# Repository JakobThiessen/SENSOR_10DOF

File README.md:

# SENSOR_10DOF

- ACC/Gyro	(BMI160/323)
- ACC/Mag	(LSM303AGR)
- T/P/RH	(BME280)

# Hardware

| Top side                |Bottom side               |
|-----------------------:|:-------------------------:|
|  |  |

| Values                 | Reference                 |
|-----------------------:|:-------------------------:|
|  |  |

# Software

**BMI160:**
```diff
+ 0x68 --> SDO to GND (default)
# 0x69 --> SDO to VDDIO
```

**BMI323:**
```diff
+ 0x68 --> SDO to GND (default)
# 0x69 --> SDO to VDDIO
```

**BME280:**
```diff
+ 0x76 --> SDO to GND (default)
# 0x77 --> SDO to VDDIO
```

**LSM303AGR:**
```diff
+ 0x3A --> ACC (default)
+ 0x3C --> MAG (default)
```

## Driver

### lsm303agr

Standard C platform-independent drivers for MEMS motion and environmental sensors
- https://www.st.com/en/embedded-software/c-driver-mems.html
- https://github.com/STMicroelectronics/x-cube-mems1

Arduino/Grove
- https://github.com/Seeed-Studio/Grove_6Axis_Accelerometer_And_Compass/blob/master/examples/CompensatedCompass.ino

embedded/lsm303agr

``` c
/* USER CODE BEGIN PV */
static struct lsm303agr_dev Sensor;

/* USER CODE BEGIN 0 */
int8_t i2c_1_read(uint8_t dev_addr, uint8_t reg_addr, uint8_t *data, uint16_t len)
{
	int8_t result;

	result = HAL_I2C_Master_Transmit(&hi2c1, (uint16_t) dev_addr, &reg_addr, 1, 10);
	result += HAL_I2C_Master_Receive(&hi2c1, (uint16_t) dev_addr, data, len, 10);
	return result;
}

int8_t i2c_1_write(uint8_t dev_addr, uint8_t reg_addr, uint8_t *data, uint16_t len)
{
	int8_t result;
	uint8_t buffer[128];

	buffer[0] = reg_addr;
	memcpy(&buffer[1], data, len);

	result = HAL_I2C_Master_Transmit(&hi2c1, (uint16_t) dev_addr, buffer, len + 1, 100);
	return result;
}

void main(void)
{
	/* Hardware init*/
	
	........
	/*  */
	Sensor.dev_addr_mag = LSM303AGR_MAG_I2C_ADDRESS;
	Sensor.dev_addr_acc = LSM303AGR_ACC_I2C_ADDRESS;
	Sensor.read = i2c_1_read;
	Sensor.write = i2c_1_write;

	struct lsm303agr_mag_data magData;
	struct lsm303agr_acc_data accData;

	int8_t res = lsm303agr_mag_init(LSM303AGR_CONTINUOUS, &Sensor);
	res = lsm303agr_acc_init(LSM303AGR_ACC_NORMAL_MODE, &Sensor);

	...

	while (1)
	{
		int8_t rslt = 0;

		rslt = lsm303agr_mag_read_data(&magData, &Sensor);
		
		uint8_t data_ready_status = 0;
		lsm303agr_acc_get_DataReadyStatus(&data_ready_status, &Sensor);
		
		if (data_ready_status != 0)
		{
			lsm303agr_acc_read_data(&accData, &Sensor);
			rslt += lsm303agr_temp_read_data(&temperature, &Sensor);
		}
	}
}

```

### BMI160/323:

- https://github.com/boschsensortec/BMI160_driver
- https://github.com/boschsensortec/BMI323-Sensor-API

## Calibration of Magnetometer with Acc-Sensor

Application note: AN3192 Using LSM303DLH for a tilt compensated electronic compass

Masterarbeit
- https://reposit.haw-hamburg.de/bitstream/20.500.12738/8460/1/Masterarbeit_Tobias_Michaelsen.pdf

Lib von ST
- https://github.com/STMicroelectronics/x-cube-mems1

Eine Sammlung von Links zu dem Thema
- https://github.com/Seeed-Studio/Grove_6Axis_Accelerometer_And_Compass/blob/master/examples/CompensatedCompass.ino

- https://www.nxp.com/docs/en/application-note/AN4248.pdf
- https://www.nxp.com/docs/en/application-note/AN4249.pdf
- https://www.st.com/resource/en/design_tip/dt0058-computing-tilt-measurement-and-tiltcompensated-ecompass-stmicroelectronics.pdf
- https://www.bosch-sensortec.com/media/boschsensortec/downloads/datasheets/bst-bmm150-ds001.pdf

## Kalmanfilter
- https://www.cbcity.de/das-kalman-filter-einfach-erklaert-teil-1
- https://www.cbcity.de/das-kalman-filter-einfach-erklaert-teil-2
- https://www.cbcity.de/4d-kalman-filter-in-c
  
- https://www.halvorsen.blog/documents/automation/kalman_filter/LabVIEW%20Kalman%20Filter%20Examples.pdf

## Rotationsmatrix
- https://www.cbcity.de/tutorial-rotationsmatrix-und-quaternion-einfach-erklaert-in-din70000-zyx-konvention

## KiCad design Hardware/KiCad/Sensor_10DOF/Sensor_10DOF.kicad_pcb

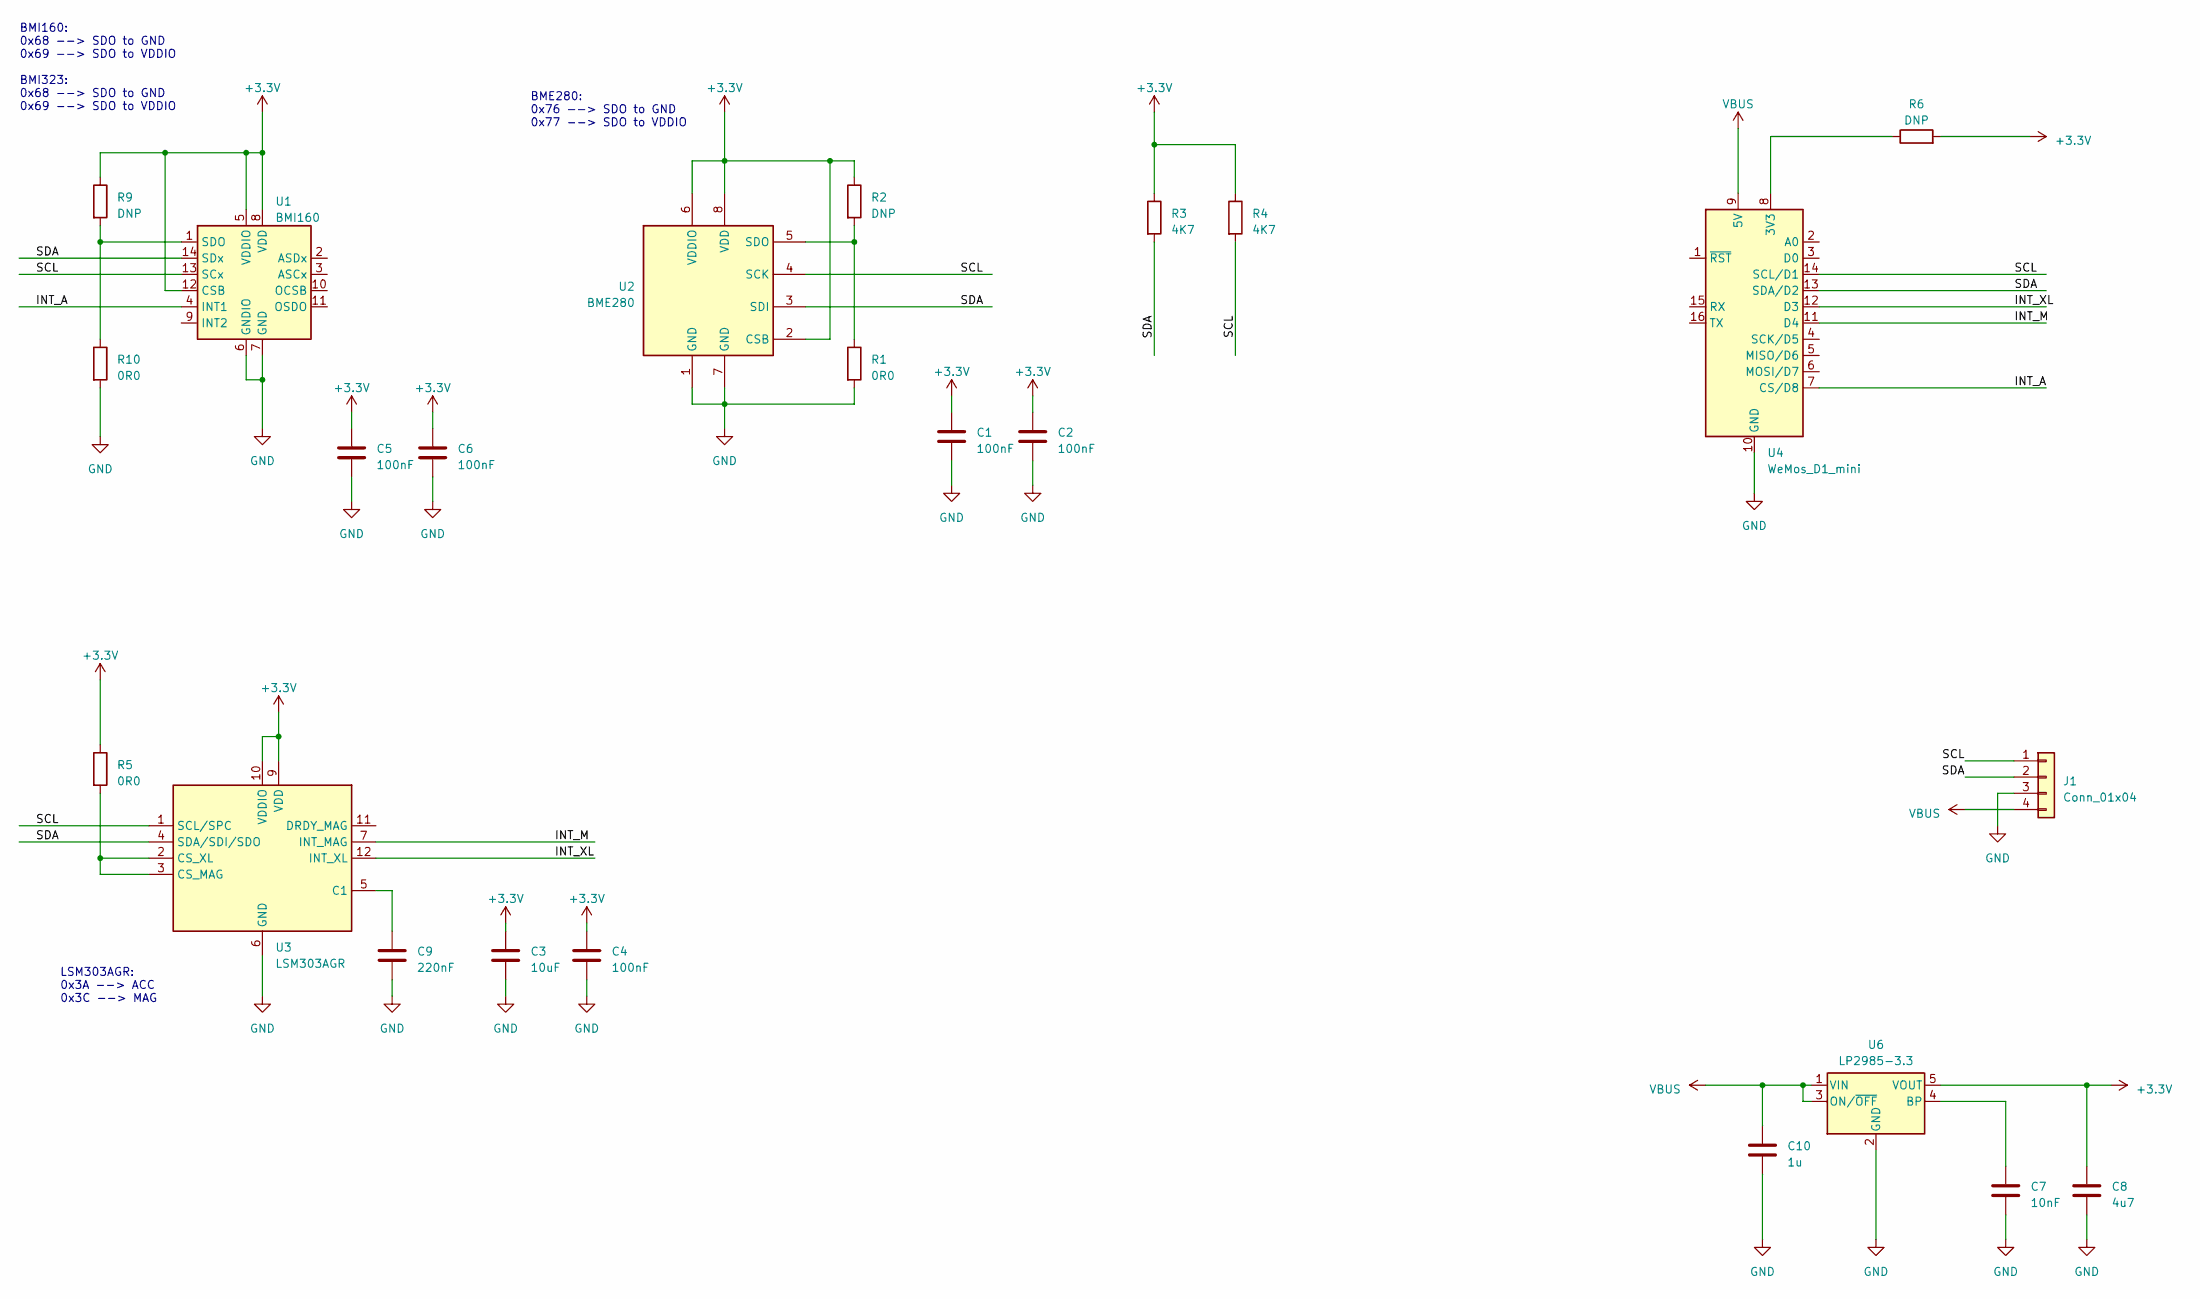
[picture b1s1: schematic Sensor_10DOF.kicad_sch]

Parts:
C1, C2, C4, C5, C6: 100nF; C_0603_1608Metric
C3: 10uF; C_0603_1608Metric
C7: 10nF; C_0603_1608Metric
C8: 4u7; C_0603_1608Metric
C9: 220nF; C_0603_1608Metric
C10: 1u; C_0603_1608Metric
J1: Conn_01x04; JST_XA_B04B-XASK-1_1x04_P2.50mm_Vertical
R1, R5, R10: 0R0; R_0402_1005Metric
R2, R6, R9: DNP; R_0402_1005Metric
R3, R4: 4K7; R_0603_1608Metric
U1: BMI160; Bosch_LGA-14_3x2.5mm_P0.5mm
U2: BME280; Bosch_LGA-8_2.5x2.5mm_P0.65mm_ClockwisePinNumbering
U3: LSM303AGR; LGA-12_2x2mm_P0.5mm
U4: WeMos_D1_mini; WEMOS_D1_mini_light
U6: LP2985-3.3; SOT-23-5

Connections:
+3.3V: C1.1, C2.1, C3.1, C4.1, C5.1, C6.1, C8.1, R2.1, R3.1, R4.1, R5.1, R6.2, R9.1, U1.5 (VDDIO), U1.8 (VDD), U1.12 (CSB), U2.2 (CSB), U2.6 (VDDIO), U2.8 (VDD), U3.9 (VDD), U3.10 (VDDIO), U6.5 (VOUT)
/INT_A: U1.4 (INT1), U4.7 (CS/D8)
/INT_M: U3.7 (INT_MAG), U4.11 (D4)
/INT_XL: U3.12 (INT_XL), U4.12 (D3)
/SCL: J1.1, R4.2, U1.13 (SCx), U2.4 (SCK), U3.1 (SCL/SPC), U4.14 (SCL/D1)
/SDA: J1.2, R3.2, U1.14 (SDx), U2.3 (SDI), U3.4 (SDA/SDI/SDO), U4.13 (SDA/D2)
GND: C1.2, C2.2, C3.2, C4.2, C5.2, C6.2, C7.2, C8.2, C9.2, C10.2, J1.3, R1.2, R10.2, U1.6 (GNDIO), U1.7 (GND), U2.1 (GND), U2.7 (GND), U3.6 (GND), U3.8 (GND), U4.10 (GND), U6.2 (GND)
unnamed: R9.2, R10.1, U1.1 (SDO)
unnamed: R1.1, R2.2, U2.5 (SDO)
unnamed: C9.1, U3.5 (C1)
unnamed: R5.2, U3.2 (CS_XL), U3.3 (CS_MAG)
unnamed: R6.1, U4.8 (3V3)
unnamed: C7.1, U6.4 (BP)
VBUS: C10.1, J1.4, U4.9 (5V), U6.1 (VIN), U6.3 (ON/~OFF)

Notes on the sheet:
BME280: 0x76 --> SDO to GND 0x77 --> SDO to VDDIO
BMI160: 0x68 --> SDO to GND 0x69 --> SDO to VDDIO BMI323: 0x68 --> SDO to GND 0x69 --> SDO to VDDIO
LSM303AGR: 0x3A --> ACC 0x3C --> MAG

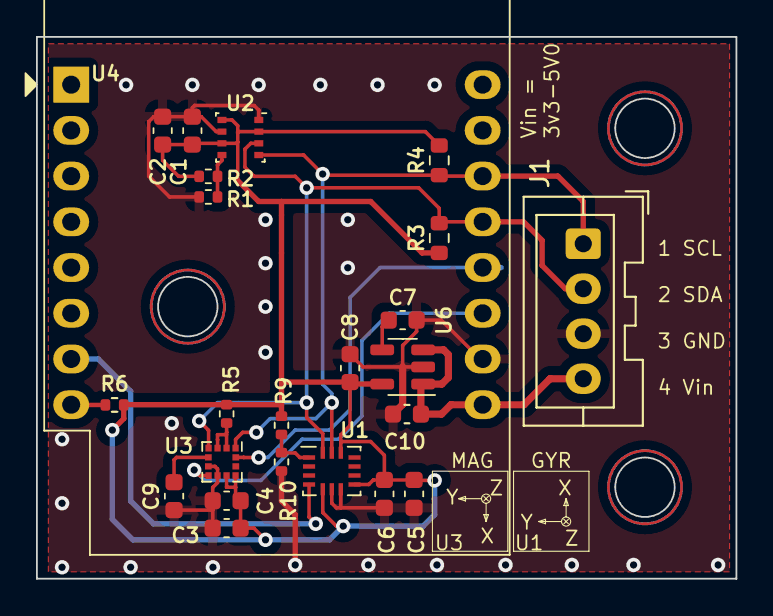
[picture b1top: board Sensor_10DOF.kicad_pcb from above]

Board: 2 copper layers, 38.9 x 30.1 mm, 24 parts (0 on the bottom side), 14 nets.

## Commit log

2023-09-29 initial
2023-09-29 deleted
2023-09-29 readme angepasst
2023-09-30 fast fertig. Pinbelegung prüfen
2023-09-30 bild hinzugefügt PCB -> text geändert
2023-09-30 Rename --> Sensor_10DOF.pdf pdf to schematic.pdf
2023-10-04 version 1.0 - release Gerberdaten erzeugt
2023-10-06 fix gerber
2023-10-07 bestückungsplan erstellt
2023-10-08 change readme.md
2024-09-27 add .gitignore
2025-03-07 add embedded folder
